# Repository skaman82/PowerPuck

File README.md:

# PowerPuck
I started this project because I was tired of my fatshark beeping and shutting down at 3.6 volts. I am using a 2s 18650 3500mAh pack. This means my batteries are still almost half full when this happens. I first just used a 9v stepup to boost the voltage, but then tracking the battery level was a pain. Then I came up with this solution. 

It not only lets you use your 18650 batteries up to 3v (per cell), it also adds voltage monitoring with adjustable alarms and a power on/off switch. On top of that the fan cable is now tidy and nice and the complete unit remains on the goggles the whole time while the battery is sitting in the pocket or on the belt.

The battery case has also a basic battery indicator - it gives a pretty good orientation of the battery state without hooking the battery up. 

# MAIN UNIT COMPONENTS

<b>Printed Case</b></br>
See 3D files directory</br>
or order it here:</br>
https://www.shapeways.com/product/Y7TP35MAT/powerpuck-case-front</br>
https://www.shapeways.com/product/XVMKZEAJ4/powerpuck-case-back</br>
</br></br>

<b>Order the PCB on jlcpcb.com (1mm thickness)</b></br>
See "PCB Files > Final Gerber" directory</br></br>

<b>ATMEGA382 AU</b></br>
<b>Y1: Xtal 16MHZ TXC 7A-16.000MAAJ-T</b></br>
<b>C1: 0,1uF cap 0603</b></br>
<b>C5: 100nF cap 0603</b></br>
<b>C3, C4: 18pF cap 0603 (2x)</b></br>
<b>10K 0603 Resistor</b></br>
<b>R3-R6: 330Ohm 0603 Resistor (4x)</b></br>
<b>D2-D4: GREEN LED 1206 (3x)</b></br>
<b>D1: 1x RED LED 1206</b></br>
<b>R1: 18K Resistor 1206</b></br>
<b>R2: 4,7K Resistor 1206</b></br>
<b>C6, C7: 10uF Cap 1206 (2x)</b></br>
<b>D6: Diode S1A</b></br>
<b>Pololu 9V Step-Up Voltage Regulator U3V12F9</b></br>
<b>Pololu Mini Pushbutton Power Switch SV</b></br>
<b>JST-SH Socket 6pin</b></br>
<b>9mm active Buzzer</b></br>
<b>8mm tact button</b></br>
<b>AMASS XT30 female plug</b></br>
<b>AMS1117/LM1117 regulator</b></br>
<b>Epoxy</b></br></br>

<b>ISCP USB Programmer like</b></br>
https://de.aliexpress.com/item/5-v-Micro-USB-Tiny-AVR-ISP-ATtiny44-USBTinyISP-Programmierer-Modul-F-r-Bootloader-ISP-Mikrocontroller/32925343387.html?spm=a2g0s.9042311.0.0.725e4c4dZq4br5</br></br>

# 18650 CASE COMPONENTS
<b>Printed Case</b></br>
See 3D files directory</br></br>

<b>2S Power-Indicator</b></br>
https://www.banggood.com/2S-3S-4S-5S-Lipo-Battery-Voltage-Display-Indicator-Board-Polymer-Power-Indicator-Panel-p-1095698.html?p=03160313547712015036</br></br>

<b>2S BMS PCB</b></br>
https://www.aliexpress.com/item/2S-7-4V-8-4V-8A-16A-18650-Lithium-Battery-Protection-Board-Current-Li-ion-2/32851804815.html?spm=a2g0s.9042311.0.0.27424c4dYKwYNW</br></br>

<b>XT30 connectors</b></br>
https://www.banggood.com/de/Tarot-RC-Helicopter-Part-Amass-One-Pair-XT30-Non-slip-Plugs-TL2918-p-954269.html?p=03160313547712015036</br></br>

<b>2S Balance plug</b></br>
https://www.banggood.com/de/Lipo-Battery-Balance-Charging-Extension-Wire-Cable-20cm-2S-3S-4S-6S-p-951866.html?p=03160313547712015036
</br>
<b>Epoxy</b></br></br>

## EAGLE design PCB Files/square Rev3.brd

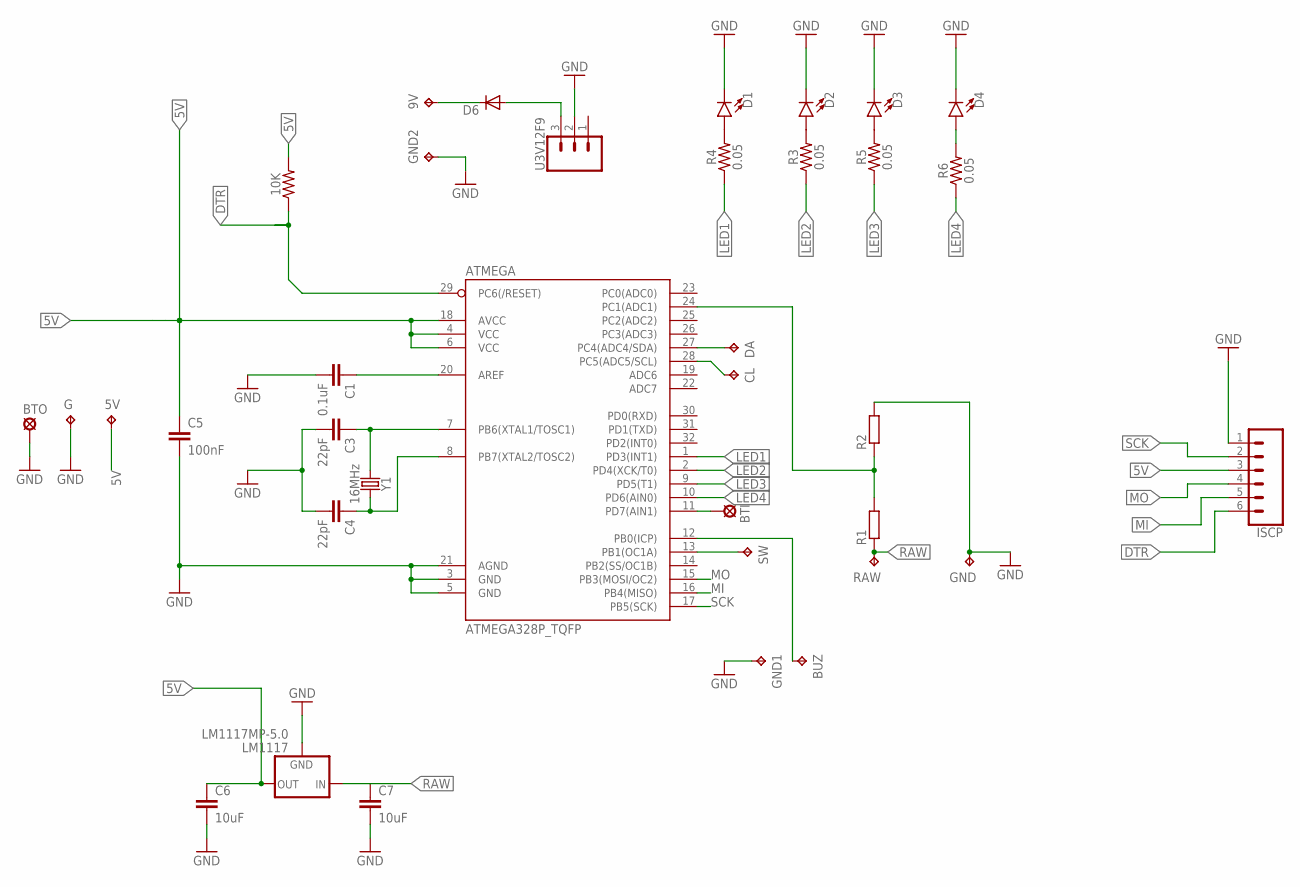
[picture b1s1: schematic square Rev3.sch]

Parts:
5V: TPB1,27; B1,27
9V: TPB2,54; B2,54
10K: 0.27OHM-0603-1/10W-1%; 0603
ATMEGA: ATMEGA328P_TQFP; TQFP32-08
BTI: LSP10
BTO: LSP10
BUZ: TPB2,54; B2,54
C1: 0.1uF; 0603
C3, C4: 22pF; 0603
C5: 100nF; 0603
C6: 10uF; 1206
C7: 10uF; C1206
CL: TPB1,27; B1,27
D1, D2, D3, D4: LED1206; LED-1206
D6: DIODE-SOD106A-R; SOD106A-R
DA: TPB1,27; B1,27
G: TPB1,27; B1,27
GND, GND1, GND2: TPB2,54; B2,54
ISCP: CONN_06SMD-1MM; 1X06-1MM
LM1117: LM1117MP-5.0; SOT223
R1, R2: R-EU_R1206; R1206
R3, R4, R5, R6: 0.05; 0603
RAW: TPB2,54; B2,54
SW: TPB1,27; B1,27
U3V12F9: CONN_03; 1X03
Y1: 16MHz; CRYSTAL-SMD-5X3.2-2PAD

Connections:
5V: 5V.TP, 10K.2, ATMEGA.4 (VCC), ATMEGA.6 (VCC), ATMEGA.18 (AVCC), C5.1, C6.1, ISCP.3, LM1117.2 (OUT), LM1117.4 (OUT)
9VOUT: D6.A, U3V12F9.3
AREF: ATMEGA.20 (AREF), C1.1
BUTTON: ATMEGA.11 (PD7(AIN1)), BTI.MP
BUZZER: ATMEGA.12 (PB0(ICP)), BUZ.TP
DTR: 10K.1, ATMEGA.29 (PC6(/RESET)), ISCP.6
GND: ATMEGA.3 (GND), ATMEGA.5 (GND), ATMEGA.21 (AGND), BTO.MP, C1.2, C3.2, C4.2, C5.2, C6.2, C7.2, D1.C, D2.C, D3.C, D4.C, G.TP, GND.TP, GND1.TP, GND2.TP, ISCP.1, LM1117.1 (GND), R2.2, U3V12F9.2
GREEN1: D2.A, R3.2
GREEN2: D3.A, R5.2
GREEN3: D4.A, R6.2
LED1: ATMEGA.1 (PD3(INT1)), R4.1
LED2: ATMEGA.2 (PD4(XCK/T0)), R3.1
LED3: ATMEGA.9 (PD5(T1)), R5.1
LED4: ATMEGA.10 (PD6(AIN0)), R6.1
MI: ATMEGA.16 (PB4(MISO)), ISCP.5
MO: ATMEGA.15 (PB3(MOSI/OC2)), ISCP.4
unnamed: ATMEGA.13 (PB1(OC1A)), SW.TP
unnamed: 9V.TP, D6.C
RAW: C7.1, LM1117.3 (IN), R1.1, RAW.TP
RED: D1.A, R4.2
SCK: ATMEGA.17 (PB5(SCK)), ISCP.2
SCL: ATMEGA.28 (PC5(ADC5/SCL)), CL.TP
SDA: ATMEGA.27 (PC4(ADC4/SDA)), DA.TP
VOLTSENS: ATMEGA.24 (PC1(ADC1)), R1.2, R2.1
XTAL1: ATMEGA.7 (PB6(XTAL1/TOSC1)), C3.1, Y1.P$1 (1)
XTAL2: ATMEGA.8 (PB7(XTAL2/TOSC2)), C4.1, Y1.P$2 (2)

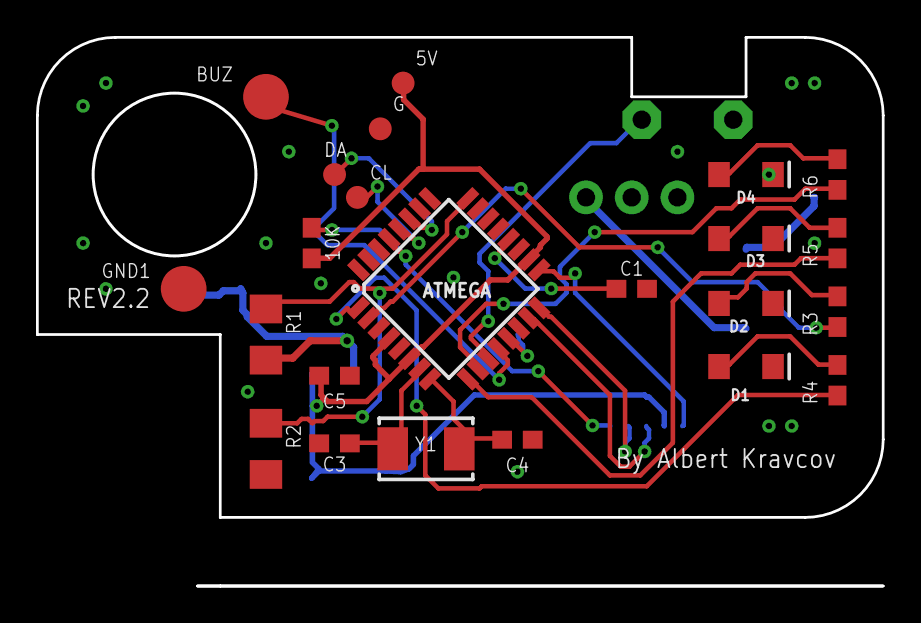
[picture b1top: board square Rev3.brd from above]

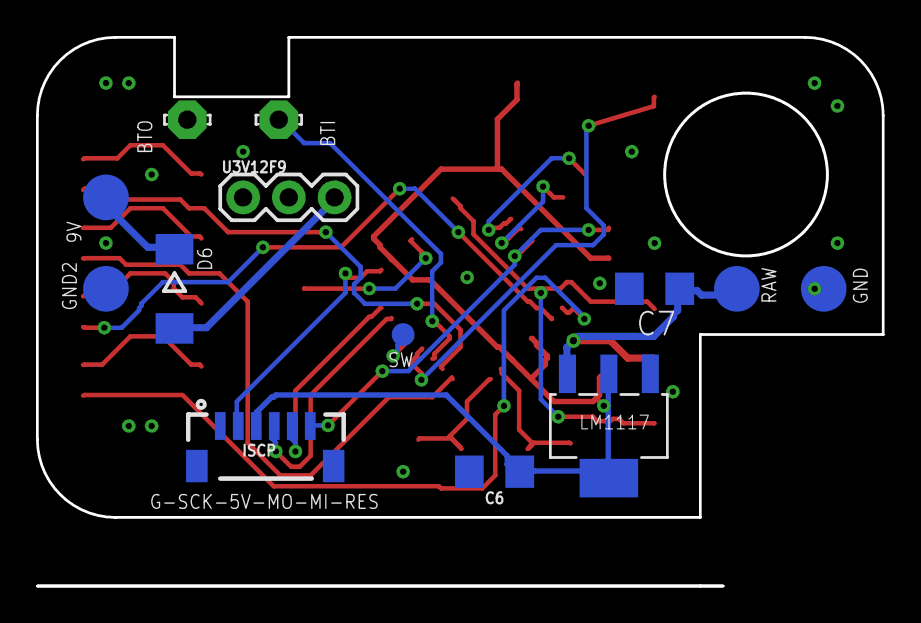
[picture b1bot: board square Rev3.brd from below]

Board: 2 copper layers, 47.0 x 30.5 mm, 36 parts (13 on the bottom side), 26 nets.

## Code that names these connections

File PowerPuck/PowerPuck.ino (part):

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  analogReference(DEFAULT);

  pinMode(3, OUTPUT); //LED red
  pinMode(4, OUTPUT); //LED green1
  pinMode(5, OUTPUT); //LED green2
  pinMode(6, OUTPUT); //LED green3
  pinMode(8, OUTPUT); //Buzzer
  pinMode(9, OUTPUT); //power
  digitalWrite(9, HIGH); //power on
  pinMode(BUTTON_PIN, INPUT_PULLUP);
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
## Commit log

2018-11-15 18650 Case STL files
2018-11-15 PCB Files
2018-11-23 Initial Code
2018-11-23 PCB rev3
2018-11-26 deadband for voltage change
2018-11-26 library upload
2018-11-26 2nd stage filter
2018-11-26 BEC PCB and first 3D work on the Case
2018-11-27 some 3d work
2018-11-27 New UI structure
2018-11-28 startup/shutdown tone
2018-11-29 new form factor
2018-11-29 some pcb adjustments
2018-11-29 another pcb version
2018-11-29 Minor PCB update
2018-11-29 small fix
2018-12-11 File update
2018-12-11 added image
2018-12-11 Updated parts
2018-12-20 PCB updates
2018-12-20 pic update
2018-12-20 photos
2018-12-26 oled mode
2018-12-28 initial oled code
2018-12-28 added comment
2018-12-28 OLED layout
2019-01-04 voltage readout improvements
2019-01-08 OLED case version
2019-01-08 OLED connection

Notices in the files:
parts and their libraries:
SparkFun-IC-Microcontroller: Licensing: Creative Commons ShareAlike 4.0 International - https://creativecommons.org/licenses/by-sa/4.0
